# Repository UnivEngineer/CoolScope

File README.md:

# CoolScope
Telescope fan controller

CoolScope is a diy 2-channel fan controller based on Arduino Nano. It is used to cool down (thermostabilize) the 12 inch Meade LX200 telescope, but can be adapted to any other scope. It is assembled in a 3D printed case and mounted on the back on the scope. The device features 2 channels for 12V PWM fans, 4 temperature sensors DS18B20 (mounted on the scope's primary mirror, inside the scope's tube, inside device's case, and one external sensor connected via 3.5 mm jack), and 1602 LCD/OLED display to show stats and menu. The device is powered by 12V external power source, and draws up to 400 mA (depending on used fans).

The project consists of three parts:

Telescope_fans - Arduino sketch source code.
PCB - KiCad files of circuit schematics and PCB.
Case - SolidWorks and STL files of 3D model of the case.

The device can use any 80 mm 1602 LCD module with parallel interface (4 data lines). The best choice for astronomy accessory is a module with red symbols on a black background. Even better choice is a red Winstar 1602 OLED (WEH001602A), fully compatible electrically with LCD modules. OLED display performance is perfect at freezing temperatures, unlike STN LCD. The device supports both types of displays, there is a jumper on the PCB to tell the software which type of display module is connected.

The Arduino Nano can either be soldered to the main PCB through its PLS pins, or installed in a DIP socket, but you have to cut and solder pins directly to Nano, otherwise it may not fit under the display module.

The device has the circuit which protects it against wrong power polarity, and power voltage monitor, which can be used to control telescope's battery charge, and also used by software to auto-save settings to EEPROM memory on power loss.

----------------------------------------------------------------------------------

Short usage manual (v 1.5)

Device has 4 buttons: [menu], [<], [>], [ok].

Once powered up, you will see the info screen. It displays current temperatures reported by sensors, fans speed and duty, and power supply voltage. You may scroll through info screen modes by pressing [<] and [>] buttons. Legend:

- A - ambient temperature, i.e. sensor inside the device
- E - external temperature, i.e. external sensor connected via jack
- M - mirror temperature
- T - tube temperature (air inside the tube)
- [battery symbol] - power supply voltage
- [rotating fan symbol] - max of (front, rear) fans duty/RPM
- F - front fan duty/RPM
- R - rear fan duty/RPM

Pressing [menu] or [ok] button will bring up the settings. Press buttons [<] or [>] to scroll through options or increase/decrease values, [ok] to enter sub-level, [menu] to return back to upper level. The settings menu hierarchy is the following:

Settings
- Cooling
  - Fans enabled [values are "off", "on"]
  - Mode once cooled [values are "Keep delta T", "Keep blowing", "Keep drawing", "Stop"]
  - Target delta T [values are 0.05, 0.1, 0.2 ... 3.0 °C]
  - Cooling speed [values are 5, 10, 15 ... 100 %]
  - Keeping speed [values are 5, 10, 15 ... 100 %]
  - Pos. pressure [values are 0, 5, 10, 15 ... 100 %]
- Sensors
  - Target delta T pair [values are "Mirror and Ambient", "Mirror and External", "Mirror and Tube"]
  - Assign sensors [scroll through list of detected DS18B20 addresses and press [menu] to assign]
    - Mirror
    - Tube
    - Ambient
    - External
- Display
  - Brightness [values are 0, 1, ... 10]
  - Contrast [LCD only; values are 1, ... 10]
  - Timeout [values are "Disabled", 5, 10, 15, ..., 120 seconds]
  - Test [all pixels of display are filled until [menu] is pressed]
- Information
  - Uptime [uptime in days hours:minutes:seconds]
  - Fan stuck alarm [values are "off", "on"]
  - Low battery alarm [values are "off", "on"]
  - Battery alarm voltage [values are 8.0, 8.1, ... 12.0 volts]
  - Power voltage [current power supply voltage]
  - About

Pressing and holding the menu button, while on the info screen, will disable/enable cooling (the message "Fans enabled"/"Fans disabled" is displayed for a few seconds). This is a quicker way to stop fans than accessing "Cooling->Fans enabled" menu.

Depending on "Display->Timeout" settings, the display may turn off after a while (if LCD is used, only back-light will turn off). To turn on it back, simply press any button.

The device will run fans at "Cooling->Cooling speed" duty until specified delta T is reached. After that, it will either stop fans or keep them spinning at "Cooling->Keeping speed". Typically, you need the primary mirror of your scope to be in thermal equilibrium with outside air, so the "Target delta T pair" must be set to "Mirror and External", and external DS18B20 sensor plugged into the 3.5 mm jack. The "Ambient" sensor is mounted inside the device, thus may report higher temperatures because of observer breathing. For a balcony observations, the "Mirror and Tube" pair may give better results, because air at balcony is warmer than the outside air anyway.

To protect interior of the scope from the dust, intake fans must be covered with dust filters (HEPA is the best solution). Also it is important to keep the pressure inside the tube a bit higher than the atmosphere, otherwise unfiltered air with dust particles may be sucked in from holes and slits. Thus intake fans must spin somewhat faster that exhaust fans. The "Cooling->Pos. pressure" menu sets the percentage of the exhaust fans speed in relation to intake fans speed. Typical value is 30-50%. You can find it experimentally using a plastic bag capping the eyepiece slot of your scope: the bag must inflate.

V 1.2 - added auto switch to external sensor, then plugged in; added CRC check of data read from sensors.
V 1.3 - added support for graphical Winstar OLED (100x16 pixels) as a define, switch OLED/LCD is not supported in this case.
V 1.4 - fixed bug with "About" menu not working properly.
V 1.5 - added exhaust fans duty adjust.

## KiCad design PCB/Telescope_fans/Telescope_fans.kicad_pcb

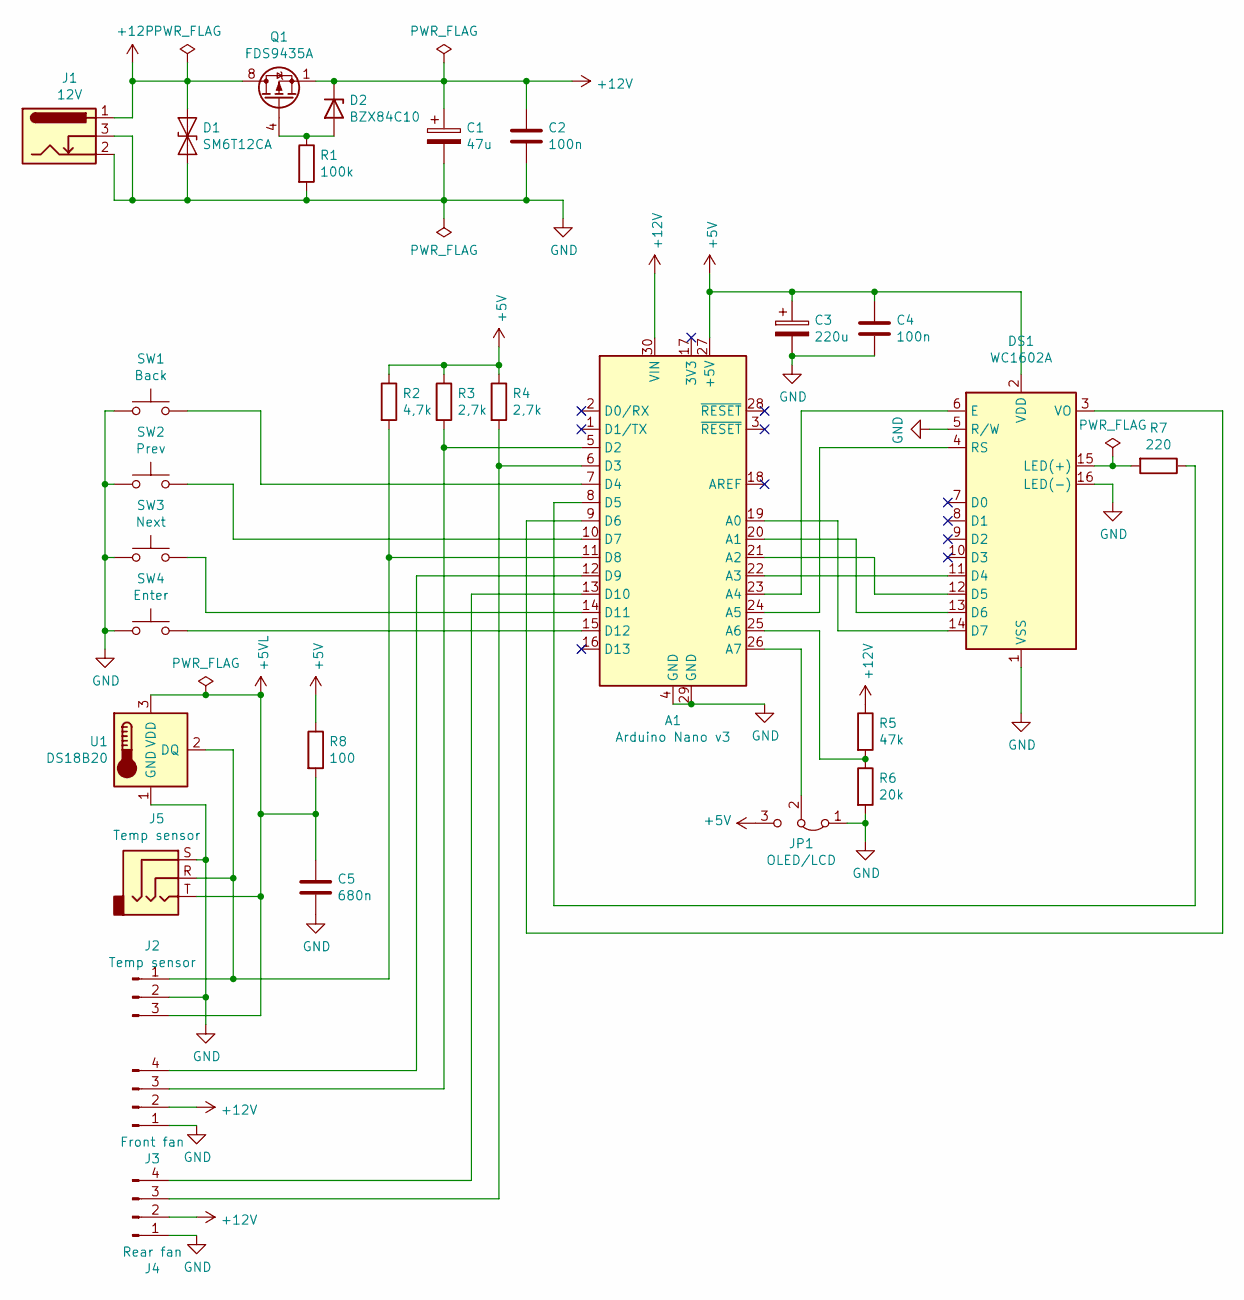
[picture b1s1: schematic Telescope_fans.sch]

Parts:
A1: Arduino Nano v3; Arduino_Nano_Chinese
C1: 47u; CP_Radial_D5.0mm_P2.50mm
C2, C4: 100n; C_0805_2012Metric_Pad1.18x1.45mm_HandSolder
C3: 220u; CP_Radial_D5.0mm_P2.50mm
C5: 680n; C_0805_2012Metric_Pad1.18x1.45mm_HandSolder
D1: SM6T12CA; D_SMB_Handsoldering
D2: BZX84C10; D_SOT-23_ANK
DS1: WC1602A
J1: 12V; BarrelJack_Horizontal
J2: Temp sensor; PinHeader_1x03_P2.54mm_Vertical
J3: Front fan; PinHeader_1x04_P2.54mm_Vertical
J4: Rear fan; PinHeader_1x04_P2.54mm_Vertical
J5: Temp sensor; Jack_3.5mm_CUI_SJ1-3533NG_Horizontal
JP1: OLED/LCD; PinHeader_1x03_P2.54mm_Vertical
Q1: FDS9435A; SOIC-8_3.9x4.9mm_P1.27mm
R1: 100k; R_0805_2012Metric_Pad1.20x1.40mm_HandSolder
R2: 4,7k; R_0805_2012Metric_Pad1.20x1.40mm_HandSolder
R3, R4: 2,7k; R_0805_2012Metric_Pad1.20x1.40mm_HandSolder
R5: 47k; R_0805_2012Metric_Pad1.20x1.40mm_HandSolder
R6: 20k; R_0805_2012Metric_Pad1.20x1.40mm_HandSolder
R7: 220; R_0805_2012Metric_Pad1.20x1.40mm_HandSolder
R8: 100; R_0805_2012Metric_Pad1.20x1.40mm_HandSolder
SW1: Back; SW_PUSH_6mm_H13mm
SW2: Prev; SW_PUSH_6mm_H13mm
SW3: Next; SW_PUSH_6mm_H13mm
SW4: Enter; SW_PUSH_6mm_H13mm
U1: DS18B20; TO-92L_Inline_Wide

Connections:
+5V: A1.27 (+5V), C3.1, C4.1, DS1.2 (VDD), JP1.3 (B), R2.1, R3.1, R4.1, R8.1
+5VL: C5.1, J2.3, J5.T, R8.2, U1.3 (VDD)
+12P: D1.1 (A1), J1.1, Q1.5 (D), Q1.6 (D), Q1.7 (D), Q1.8 (D)
+12V: A1.30 (VIN), C1.1, C2.1, D2.1 (K), J3.2, J4.2, Q1.1 (S), Q1.2 (S), Q1.3 (S), R5.1
GND: A1.4 (GND), A1.29 (GND), C1.2, C2.2, C3.2, C4.2, C5.2, D1.2 (A2), DS1.1 (VSS), DS1.5 (R/W), DS1.16 (LED(-)), J1.2, J1.3, J2.2, J3.1, J4.1, J5.S, JP1.1 (A), R1.2, R6.2, SW1.1, SW2.1, SW3.1, SW4.1, U1.1 (GND)
unnamed: A1.5 (D2), J3.3, R3.2
unnamed: A1.6 (D3), J4.3, R4.2
unnamed: A1.7 (D4), SW1.2
unnamed: A1.8 (D5), R7.1
unnamed: A1.9 (D6), DS1.3 (VO)
unnamed: A1.10 (D7), SW2.2
unnamed: A1.11 (D8), J2.1, J5.R, R2.2, U1.2 (DQ)
unnamed: A1.12 (D9), J3.4
unnamed: A1.13 (D10), J4.4
unnamed: A1.14 (D11), SW3.2
unnamed: A1.15 (D12), SW4.2
unnamed: A1.19 (A0), DS1.14 (D7)
unnamed: A1.20 (A1), DS1.13 (D6)
unnamed: A1.21 (A2), DS1.12 (D5)
unnamed: A1.22 (A3), DS1.11 (D4)
unnamed: A1.23 (A4), DS1.6 (E)
unnamed: A1.24 (A5), DS1.4 (RS)
unnamed: A1.25 (A6), R5.2, R6.1
unnamed: A1.26 (A7), JP1.2 (C)
unnamed: D2.2 (A), Q1.4 (G), R1.1
unnamed: DS1.15 (LED(+)), R7.2

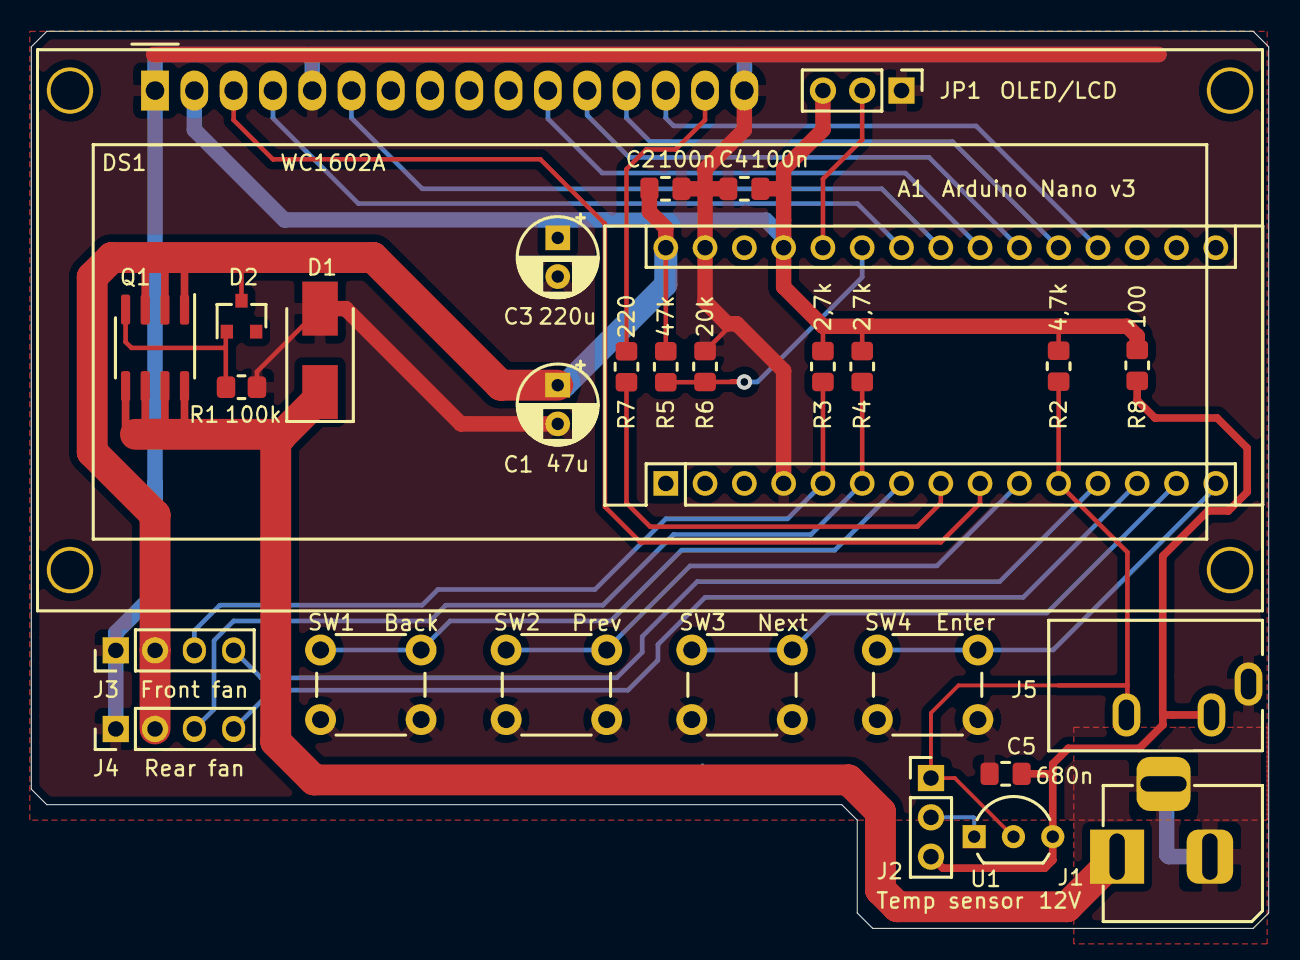
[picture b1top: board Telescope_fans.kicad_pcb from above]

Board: 2 copper layers, 80.0 x 58.0 mm, 29 parts (0 on the bottom side), 26 nets.

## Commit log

2021-09-15 Arduino sketch
    "Firmware" for the CoolScope fan controller. Will be updated.
2021-09-15 PCB project for KiCad
    Schematics and PCB project for KiCad
2021-09-15 Case drawing project for SolidWorks
    Case, buttons and hole dummy project for SolidWorks. Includes STL files for 3D printing, and dxf files exported from the PCB project to use as a sketch.
2021-09-19 v 1.1
2021-09-20 V 1.2
2023-05-02 V 1.3
    Support of graphical Winstar OLED 100x16 with custom font
2023-05-03 Added Russian language
2024-05-31 Fixed info/about in Russian mode
2025-05-26 V1.5
    - Added exhaust fans percentage settings
    - fixed typos in readme
